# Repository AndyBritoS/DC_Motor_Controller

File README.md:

# DC_Motor_Controller
DC Motor Controller PCB Project files

This project was made following the PCB Design Mastery course from Fresu Electronics (https://www.fresuelectronics.com/) and it is for demonstration purpose only. The hardware was not built or tested. Some design aspects were ignored.

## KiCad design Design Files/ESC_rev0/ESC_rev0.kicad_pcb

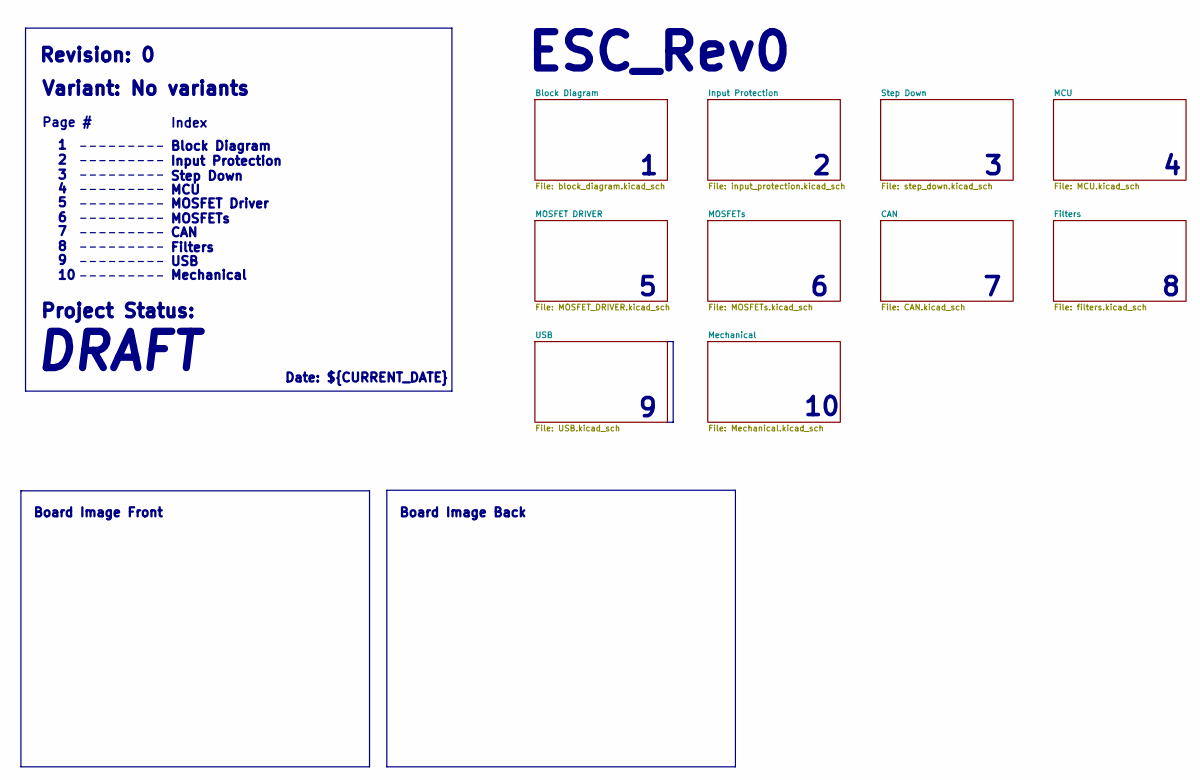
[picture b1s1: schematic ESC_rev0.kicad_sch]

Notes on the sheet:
MOSFET Driver
${TITLE}
Filters
Block Diagram
Revision: ${REVISION}
USB
Index
DRAFT
Mechanical
Page #
MOSFETs
Step Down
Variant: No variants
CAN
Input Protection
MCU
Board Image Front
Date: ${CURRENT_DATE}
Board Image Back
Project Status:

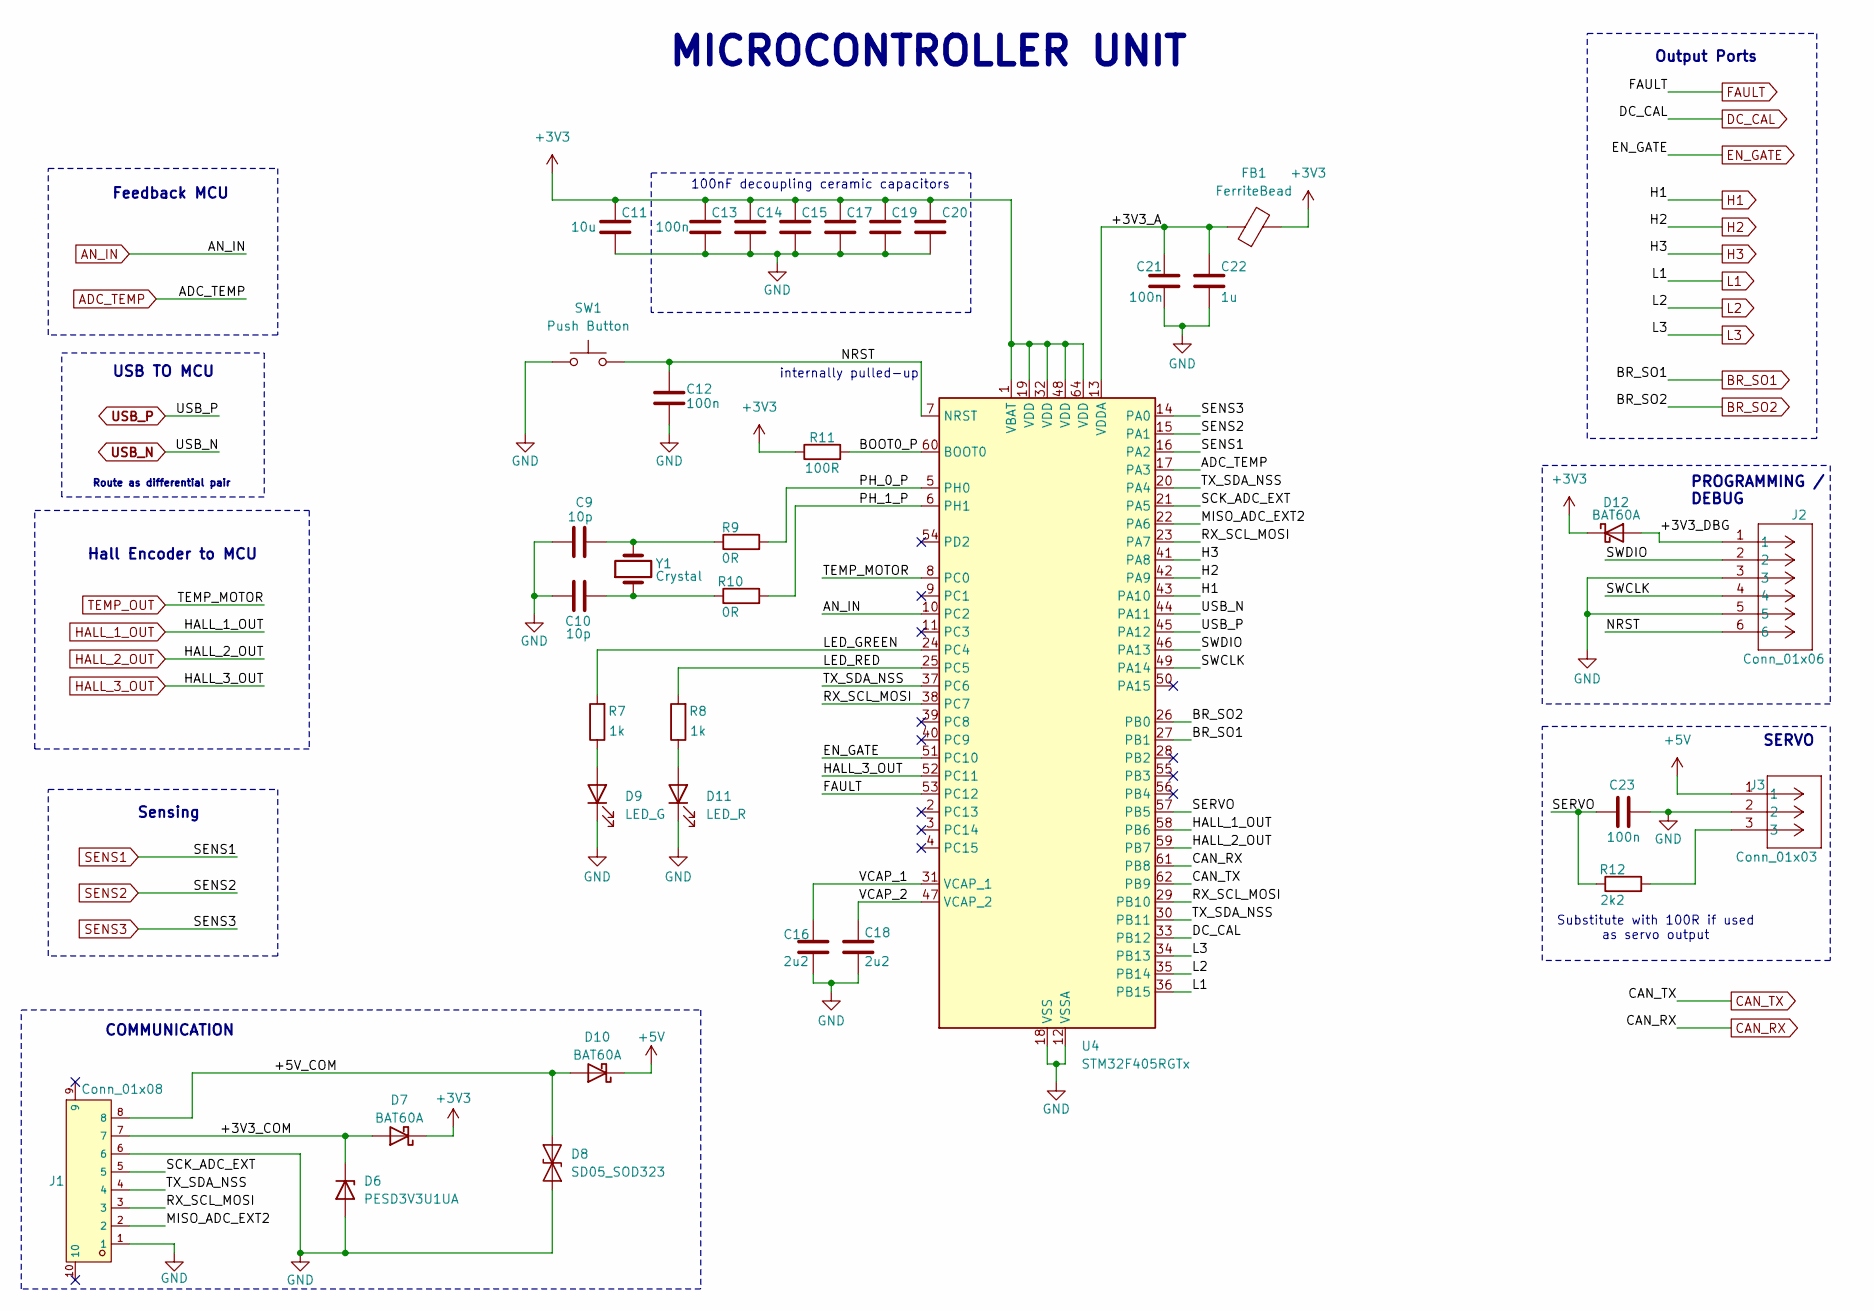
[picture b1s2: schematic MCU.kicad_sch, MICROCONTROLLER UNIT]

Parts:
C9, C10: 10p; C_0402_1005Metric
C11: 10u; C_0603_1608Metric
C12, C13, C14, C15, C17, C19, C20, C21, C23: 100n; C_0603_1608Metric
C16, C18: 2u2; C_0603_1608Metric
C22: 1u; C_0603_1608Metric
D6: PESD3V3U1UA; D_SOD-323F
D7, D10, D12: BAT60A; D_SOD-323
D8: SD05_SOD323; D_SOD-323
D9: LED_G; LED_0201_0603Metric
D11: LED_R; LED_0201_0603Metric
FB1: FerriteBead; L_0805_2012Metric
J1: Conn_01x08; CONN-SMD_8P-P2.50_HX25003-8AWB; LCSC C442367
J2: Conn_01x06; CONN_S6B-XH-SM4-TB_JST
J3: Conn_01x03; CONN3_S3B-XH_JST
R7, R8: 1k; R_0603_1608Metric
R9, R10: 0R; R_0603_1608Metric
R11: 100R; R_0603_1608Metric
R12: 2k2; R_0603_1608Metric
SW1: Push Button; SW_PTS636_SM43J_SMTR_LFS
U4: STM32F405RGTx; LQFP-64_10x10mm_P0.5mm
Y1: Crystal; Crystal_SMD_2520-4Pin_2.5x2.0mm

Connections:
+3V3: C11.1, C13.1, C14.1, C15.1, C17.1, C19.1, C20.1, D7.1 (K), D12.1 (K), FB1.2, R11.1, U4.1 (VBAT), U4.19 (VDD), U4.32 (VDD), U4.48 (VDD), U4.64 (VDD); also elsewhere on the board
+5V: D10.1 (K), J3.1; also elsewhere on the board
/MCU/+3V3_A: C21.1, C22.1, FB1.1, U4.13 (VDDA)
/MCU/+3V3_COM: D6.1 (K), D7.2 (A), J1.7
/MCU/+3V3_DBG: D12.2 (A), J2.1
/MCU/+5V_COM: D8.2 (A2), D10.2 (A), J1.8
/MCU/BOOT0_P: R11.2, U4.60 (BOOT0)
/MCU/LED_GREEN: R7.2, U4.24 (PC4)
/MCU/LED_RED: R8.2, U4.25 (PC5)
/MCU/MISO_ADC_EXT2: J1.2, U4.22 (PA6)
/MCU/NRST: C12.1, J2.6, SW1.2, U4.7 (NRST)
/MCU/PH_0_P: R9.2, U4.5 (PH0)
/MCU/PH_1_P: R10.2, U4.6 (PH1)
/MCU/RX_SCL_MOSI: J1.3, U4.23 (PA7), U4.29 (PB10), U4.38 (PC7)
/MCU/SCK_ADC_EXT: J1.5, U4.21 (PA5)
/MCU/SERVO: C23.1, R12.1, U4.57 (PB5)
/MCU/SWCLK: J2.4, U4.49 (PA14)
/MCU/SWDIO: J2.2, U4.46 (PA13)
/MCU/TX_SDA_NSS: J1.4, U4.20 (PA4), U4.30 (PB11), U4.37 (PC6)
/MCU/VCAP_1: C16.1, U4.31 (VCAP_1)
/MCU/VCAP_2: C18.1, U4.47 (VCAP_2)
ADC_TEMP: U4.17 (PA3); also elsewhere on the board
AN_IN: U4.10 (PC2); also elsewhere on the board
BR_SO1: U4.27 (PB1); also elsewhere on the board
BR_SO2: U4.26 (PB0); also elsewhere on the board
CAN_RX: U4.61 (PB8); also elsewhere on the board
CAN_TX: U4.62 (PB9); also elsewhere on the board
DC_CAL: U4.33 (PB12); also elsewhere on the board
EN_GATE: U4.51 (PC10); also elsewhere on the board
FAULT: U4.53 (PC12); also elsewhere on the board
GND: C9.1, C10.1, C11.2, C12.2, C13.2, C14.2, C15.2, C16.2, C17.2, C18.2, C19.2, C20.2, C21.2, C22.2, C23.2, D6.2 (A), D8.1 (A1), D9.1 (K), D11.1 (K), J1.1, J1.6, J2.3, J2.5, J3.2, SW1.1, U4.12 (VSSA), U4.18 (VSS), U4.63 (VSS); also elsewhere on the board
H1: U4.43 (PA10); also elsewhere on the board
H2: U4.42 (PA9); also elsewhere on the board
H3: U4.41 (PA8); also elsewhere on the board
HALL_1_OUT: U4.58 (PB6); also elsewhere on the board
HALL_2_OUT: U4.59 (PB7); also elsewhere on the board
HALL_3_OUT: U4.52 (PC11); also elsewhere on the board
L1: U4.36 (PB15); also elsewhere on the board
L2: U4.35 (PB14); also elsewhere on the board
L3: U4.34 (PB13); also elsewhere on the board
unnamed: C9.2, R9.1, Y1.2
unnamed: C10.2, R10.1, Y1.1
unnamed: D9.2 (A), R7.1
unnamed: D11.2 (A), R8.1
unnamed: J3.3, R12.2
SENS1: U4.16 (PA2); also elsewhere on the board
SENS2: U4.15 (PA1); also elsewhere on the board
SENS3: U4.14 (PA0); also elsewhere on the board
TEMP_OUT: U4.8 (PC0); also elsewhere on the board
USB_N: U4.44 (PA11); also elsewhere on the board
USB_P: U4.45 (PA12); also elsewhere on the board

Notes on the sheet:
Substitute with 100R if used as servo output
internally pulled-up
Hall Encoder to MCU
Output Ports
USB TO MCU
Feedback MCU
PROGRAMMING / DEBUG
SERVO
${TITLE}
COMMUNICATION
100nF decoupling ceramic capacitors
Route as differential pair
Sensing

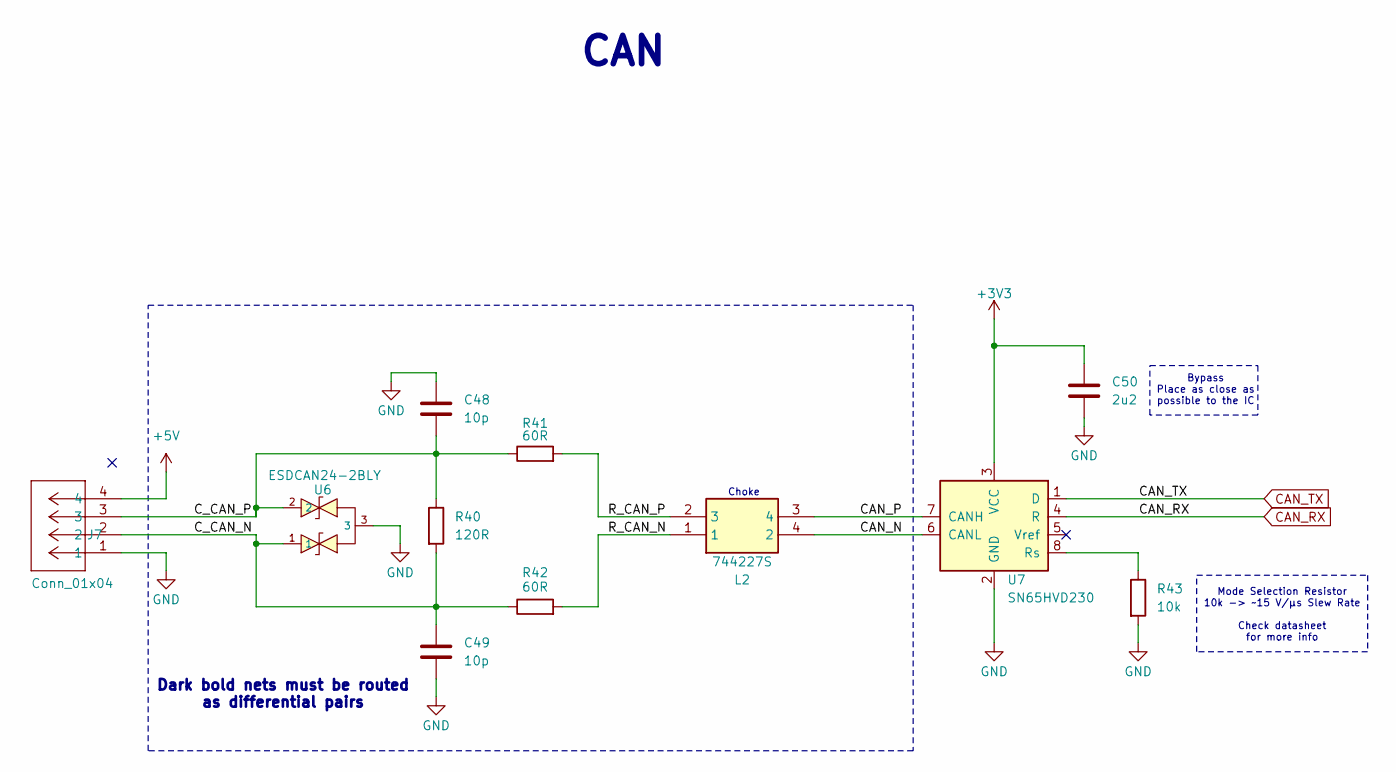
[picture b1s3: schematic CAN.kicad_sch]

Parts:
C48, C49: 10p; C_0603_1608Metric
C50: 2u2; C_0603_1608Metric
J7: Conn_01x04; CONN4_S4B-XH_JST
L2: 744227S; WE-SL274; Manufacturer_Part_Number 744227S; Mouser Part Number 710-744227S
R40: 120R; R_0603_1608Metric
R41, R42: 60R; R_0603_1608Metric
R43: 10k; R_0603_1608Metric
U6: ESDCAN24-2BLY; SOT-23-3_L3.0-W1.7-P0.95-LS2.9-BR; LCSC C246766
U7: SN65HVD230; SOIC-8_3.9x4.9mm_P1.27mm

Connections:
+3V3: C50.1, U7.3 (VCC); also elsewhere on the board
+5V: J7.4; also elsewhere on the board
/CAN/CAN_N: L2.4 (2), U7.6 (CANL)
/CAN/CAN_P: L2.3 (4), U7.7 (CANH)
/CAN/C_CAN_N: C49.1, J7.2, R40.2, R42.1, U6.1
/CAN/C_CAN_P: C48.2, J7.3, R40.1, R41.1, U6.2
/CAN/R_CAN_N: L2.1, R42.2
/CAN/R_CAN_P: L2.2 (3), R41.2
CAN_RX: U7.4 (R); also elsewhere on the board
CAN_TX: U7.1 (D); also elsewhere on the board
GND: C48.1, C49.2, C50.2, J7.1, R43.2, U6.3, U7.2 (GND); also elsewhere on the board
unnamed: R43.1, U7.8 (Rs)

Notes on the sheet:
Dark bold nets must be routed as differential pairs
Mode Selection Resistor 10k -> ~15 V/µs Slew Rate Check datasheet for more info
Bypass Place as close as possible to the IC
${TITLE}
Choke

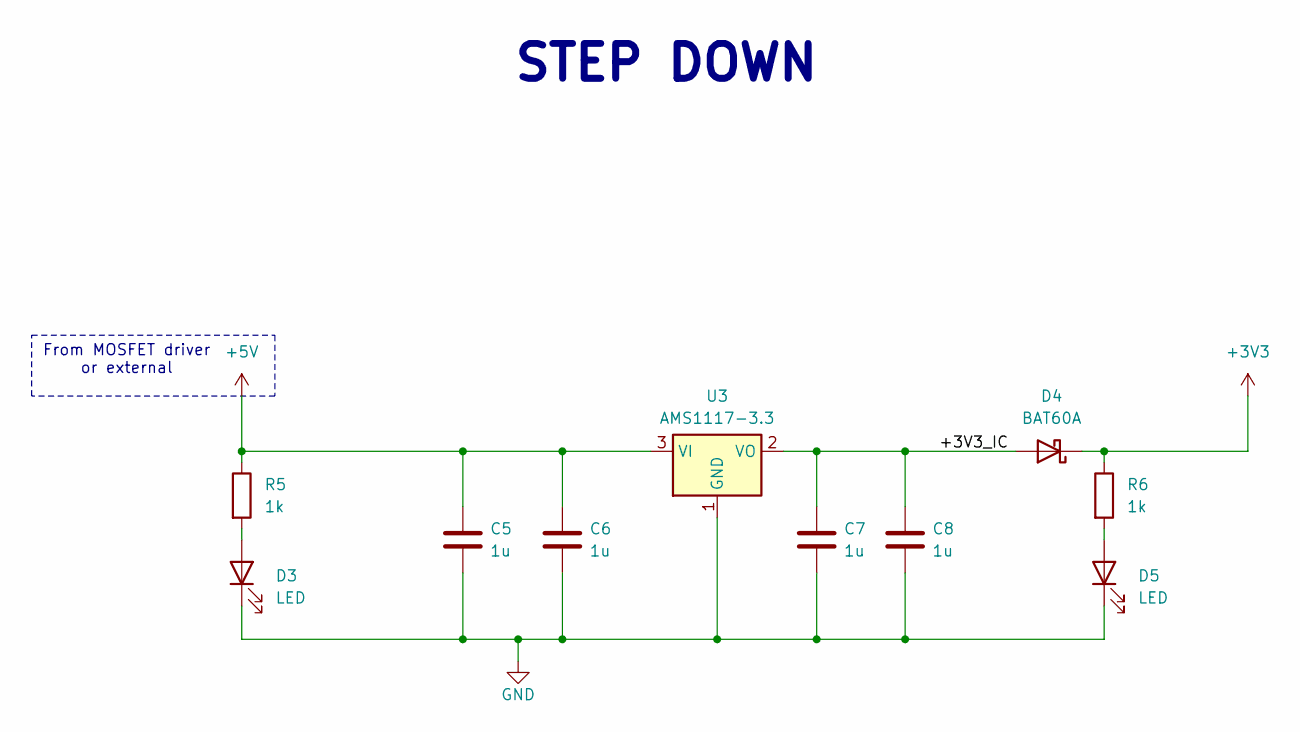
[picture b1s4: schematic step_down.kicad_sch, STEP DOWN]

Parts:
C5, C6, C7, C8: 1u; C_0603_1608Metric
D3, D5: LED; LED_0805_2012Metric
D4: BAT60A; D_SOD-323
R5, R6: 1k; R_0603_1608Metric
U3: AMS1117-3.3; SOT-223-3_TabPin2

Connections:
+3V3: D4.1 (K), R6.1; also elsewhere on the board
+5V: C5.1, C6.1, R5.1, U3.3 (VI); also elsewhere on the board
/Step Down/+3V3_IC: C7.1, C8.1, D4.2 (A), U3.2 (VO)
GND: C5.2, C6.2, C7.2, C8.2, D3.1 (K), D5.1 (K), U3.1 (GND); also elsewhere on the board
unnamed: D3.2 (A), R5.2
unnamed: D5.2 (A), R6.2

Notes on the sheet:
From MOSFET driver or external
${TITLE}

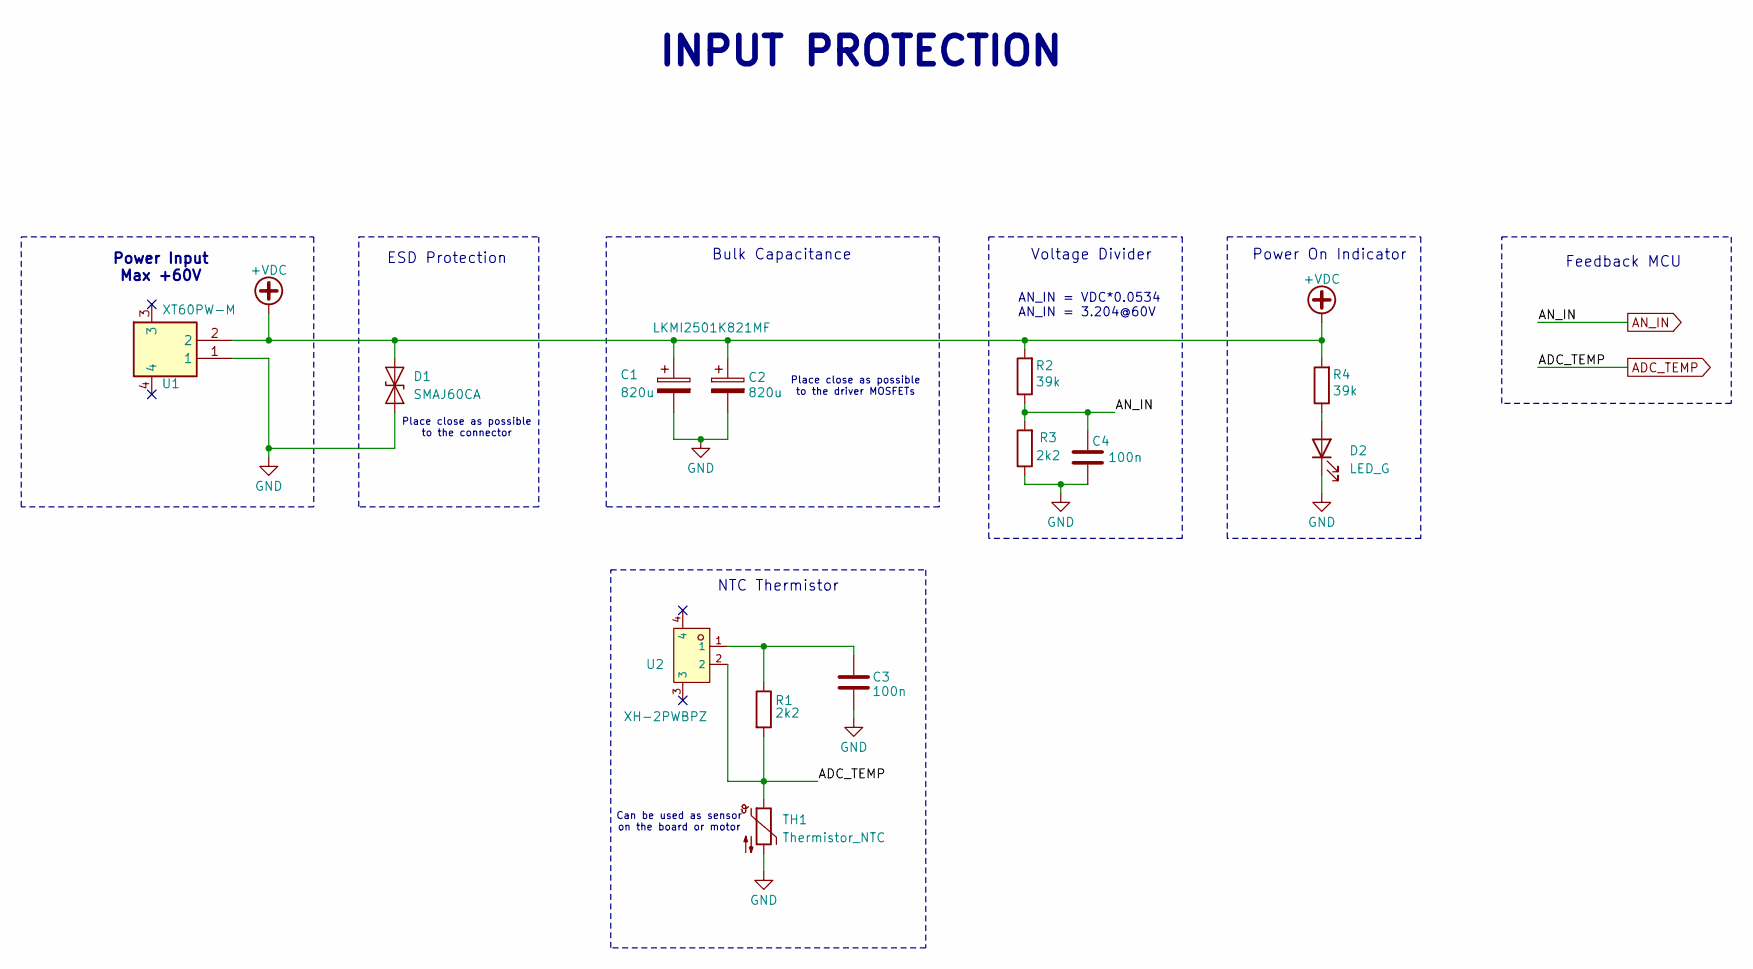
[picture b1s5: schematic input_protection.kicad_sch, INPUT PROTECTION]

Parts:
C1, C2: 820u; CP_Radial_D16.0mm_P7.50mm
C3, C4: 100n; C_0603_1608Metric
D1: SMAJ60CA; D_SMA
D2: LED_G; LED_0805_2012Metric
R1, R3: 2k2; R_0603_1608Metric
R2, R4: 39k; R_0603_1608Metric
TH1: Thermistor_NTC; C_0603_1608Metric_Pad1.08x0.95mm_HandSolder
U1: XT60PW-M; XT60PWM; Manufacturer_Part_Number XT60PW-M; LCSC C431092
U2: XH-2PWBPZ; CONN-SMD_XH-2PWBPZ; LCSC C2687444

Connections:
+VDC: C1.1, C2.1, D1.2 (A2), R2.2, R4.2, U1.2; also elsewhere on the board
ADC_TEMP: R1.2, TH1.1, U2.2; also elsewhere on the board
AN_IN: C4.1, R2.1, R3.2; also elsewhere on the board
GND: C1.2, C2.2, C3.2, C4.2, D1.1 (A1), D2.1 (K), R3.1, TH1.2, U1.1; also elsewhere on the board
unnamed: C3.1, R1.1, U2.1
unnamed: D2.2 (A), R4.1

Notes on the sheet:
Place close as possible to the driver MOSFETs
Place close as possible to the connector
Voltage Divider
AN_IN = VDC*0.0534 AN_IN = 3.204@60V
Can be used as sensor on the board or motor
Feedback MCU
Power Input Max +60V
${TITLE}
NTC Thermistor
Power On Indicator
ESD Protection
Bulk Capacitance

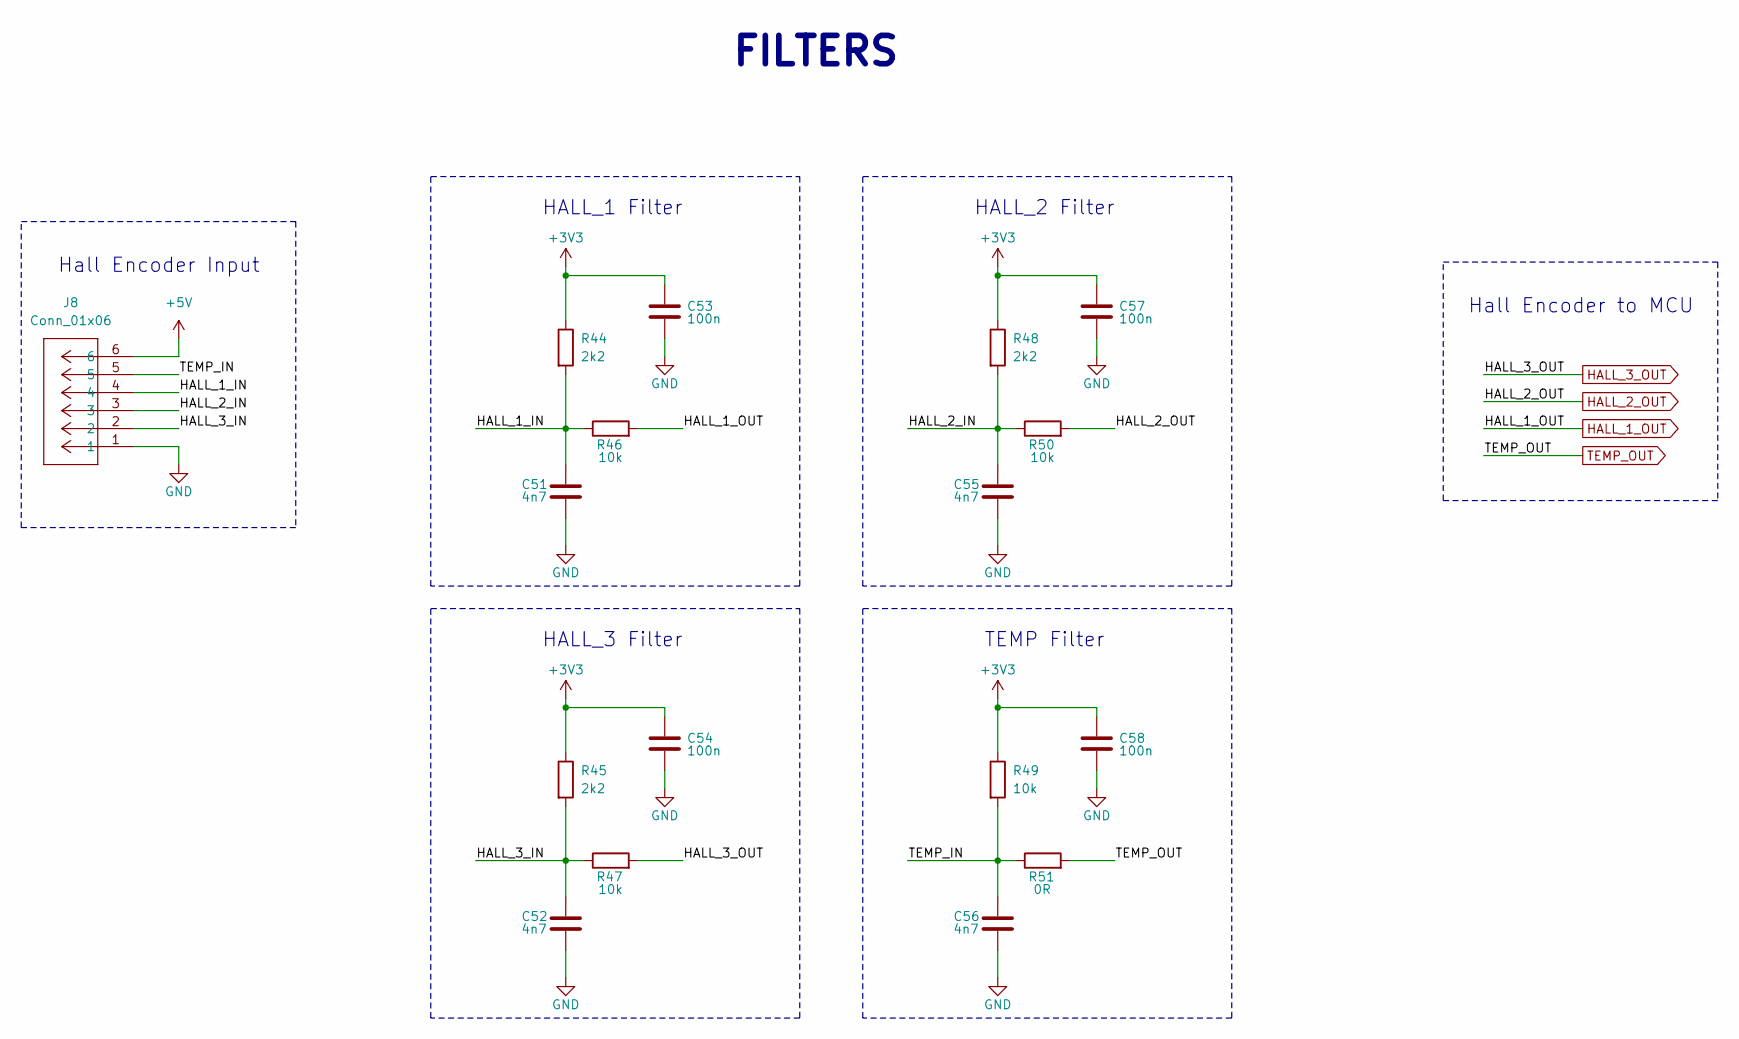
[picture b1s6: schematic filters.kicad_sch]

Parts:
C51, C52, C55, C56: 4n7; C_0603_1608Metric
C53, C54, C57, C58: 100n; C_0603_1608Metric
J8: Conn_01x06; CONN_S6B-XH-SM4-TB_JST
R44, R45, R48: 2k2; R_0603_1608Metric
R46, R47, R49, R50: 10k; R_0603_1608Metric
R51: 0R; R_0603_1608Metric

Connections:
+3V3: C53.1, C54.1, C57.1, C58.1, R44.1, R45.1, R48.1, R49.1; also elsewhere on the board
+5V: J8.6; also elsewhere on the board
/Filters/HALL_1_IN: C51.1, J8.4, R44.2, R46.1
/Filters/HALL_2_IN: C55.1, J8.3, R48.2, R50.1
/Filters/HALL_3_IN: C52.1, J8.2, R45.2, R47.1
/Filters/TEMP_IN: C56.1, J8.5, R49.2, R51.1
GND: C51.2, C52.2, C53.2, C54.2, C55.2, C56.2, C57.2, C58.2, J8.1; also elsewhere on the board
HALL_1_OUT: R46.2; also elsewhere on the board
HALL_2_OUT: R50.2; also elsewhere on the board
HALL_3_OUT: R47.2; also elsewhere on the board
TEMP_OUT: R51.2; also elsewhere on the board

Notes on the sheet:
HALL_1 Filter
Hall Encoder Input
HALL_3 Filter
HALL_2 Filter
${TITLE}
TEMP Filter
Hall Encoder to MCU

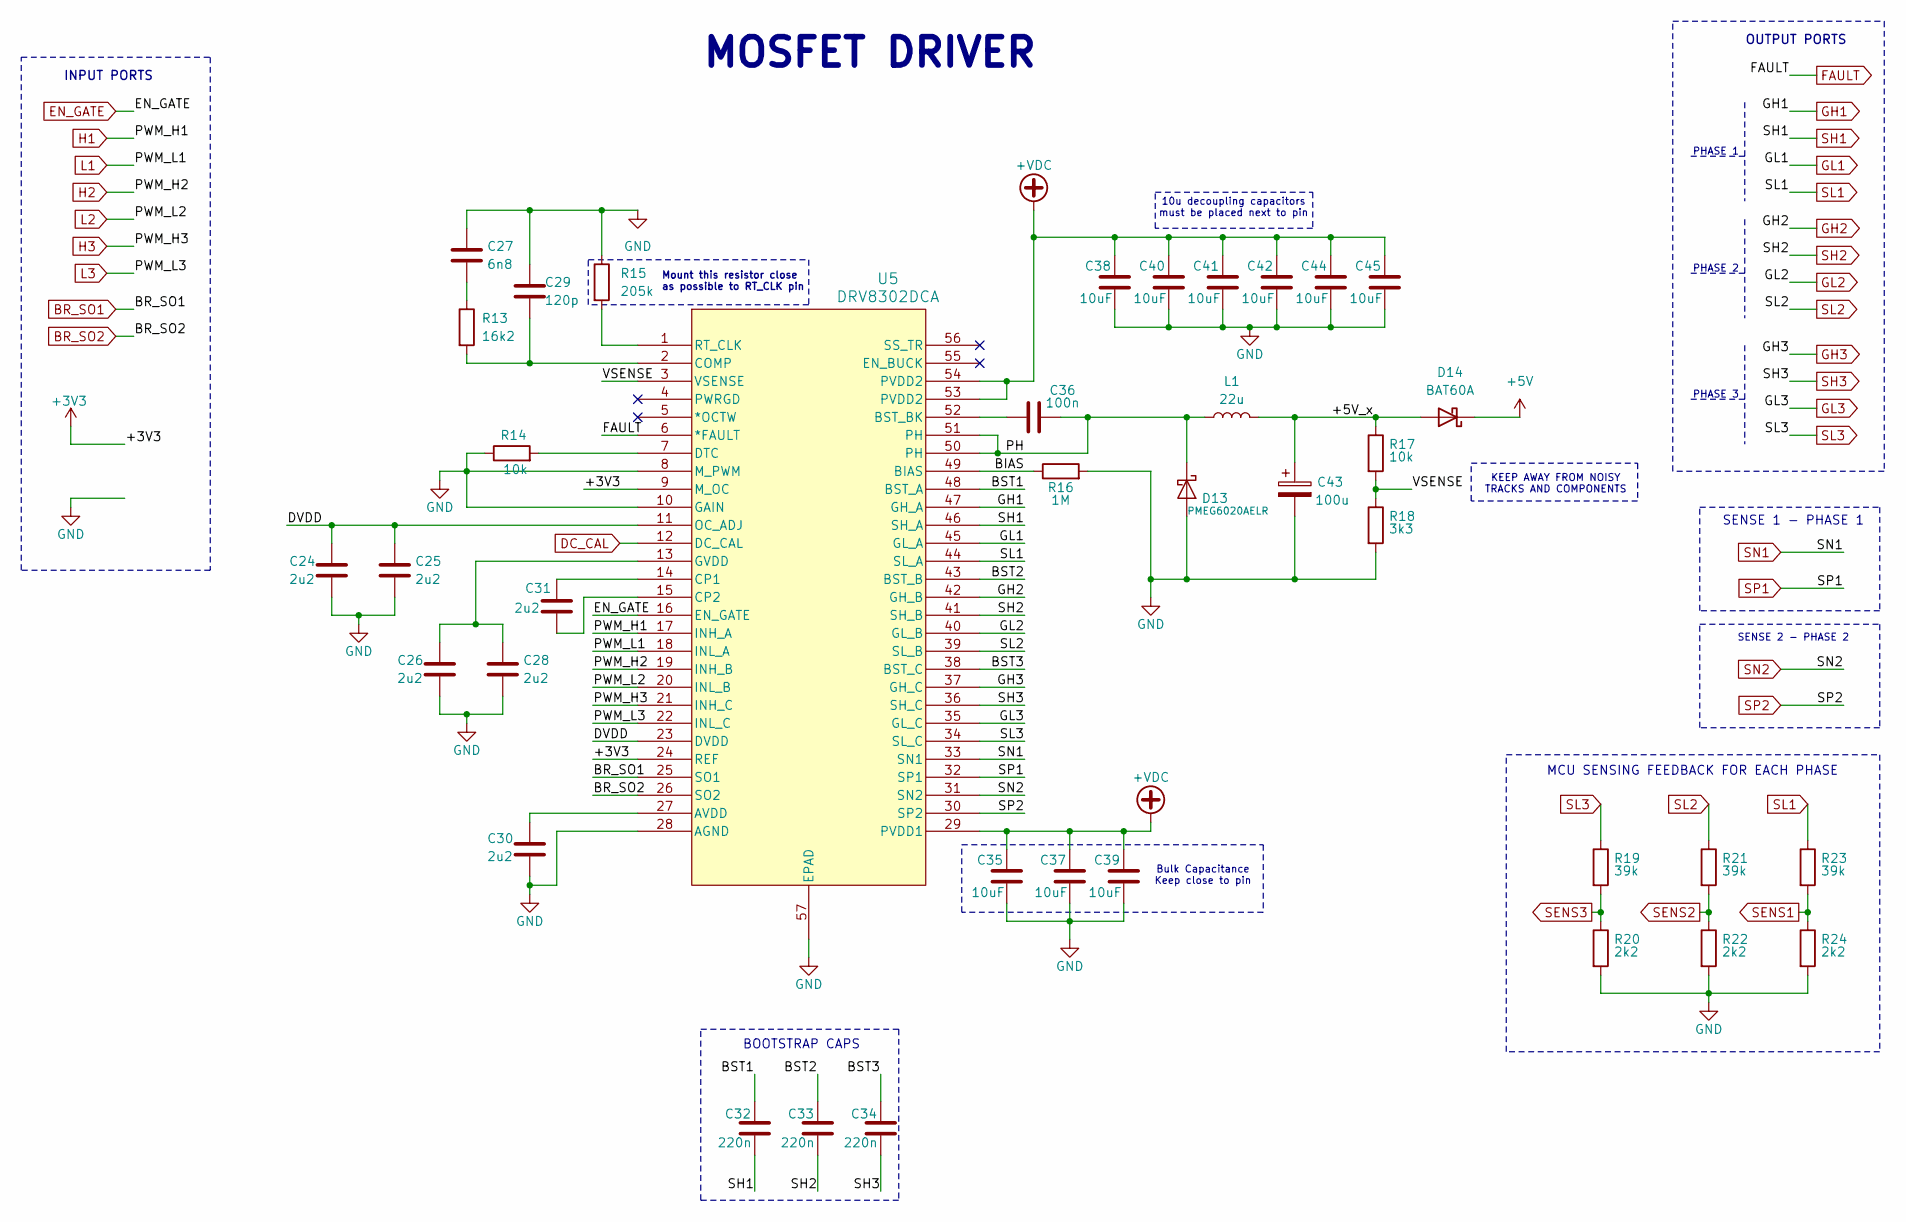
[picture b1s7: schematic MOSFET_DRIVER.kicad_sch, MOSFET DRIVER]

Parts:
C24, C25, C26, C28, C30, C31: 2u2; C_0603_1608Metric
C27: 6n8; C_0603_1608Metric
C29: 120p; C_0603_1608Metric
C32, C33, C34: 220n; C_0603_1608Metric
C35, C37, C38, C39, C40, C41, C42, C44, C45: 10uF; C_0603_1608Metric
C36: 100n; C_0603_1608Metric
C43: 100u; C_1210_3225Metric
D13: PMEG6020AELR; Nexperia_CFP3_SOD-123W
D14: BAT60A; D_SOD-323
L1: 22u; IND-SMD_L7.8-W7.8_SDR0805
R13: 16k2; R_0603_1608Metric
R14, R17: 10k; R_0603_1608Metric
R15: 205k; R_0603_1608Metric
R16: 1M; R_0603_1608Metric
R18: 3k3; R_0603_1608Metric
R19, R21, R23: 39k; R_0603_1608Metric
R20, R22, R24: 2k2; R_0603_1608Metric
U5: DRV8302DCA; DCA56_6P35X3P61

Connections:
+3V3: U5.9 (M_OC), U5.24 (REF); also elsewhere on the board
+5V: D14.1 (K); also elsewhere on the board
+VDC: C35.1, C37.1, C38.1, C39.1, C40.1, C41.1, C42.1, C44.1, C45.1, U5.29 (PVDD1), U5.53 (PVDD2), U5.54 (PVDD2); also elsewhere on the board
/MOSFET DRIVER/+5V_x: C43.1, D14.2 (A), L1.2, R17.1
/MOSFET DRIVER/BIAS: R16.1, U5.49 (BIAS)
/MOSFET DRIVER/BST1: C32.1, U5.48 (BST_A)
/MOSFET DRIVER/BST2: C33.1, U5.43 (BST_B)
/MOSFET DRIVER/BST3: C34.1, U5.38 (BST_C)
/MOSFET DRIVER/DVDD: C24.1, C25.1, U5.11 (OC_ADJ), U5.23 (DVDD)
/MOSFET DRIVER/PH: C36.2, D13.1 (K), L1.1, U5.50 (PH), U5.51 (PH)
/MOSFET DRIVER/VSENSE: R17.2, R18.1, U5.3 (VSENSE)
BR_SO1: U5.25 (SO1); also elsewhere on the board
BR_SO2: U5.26 (SO2); also elsewhere on the board
DC_CAL: U5.12 (DC_CAL); also elsewhere on the board
EN_GATE: U5.16 (EN_GATE); also elsewhere on the board
FAULT: U5.6 (*FAULT); also elsewhere on the board
GH1: U5.47 (GH_A); also elsewhere on the board
GH2: U5.42 (GH_B); also elsewhere on the board
GH3: U5.37 (GH_C); also elsewhere on the board
GL1: U5.45 (GL_A); also elsewhere on the board
GL2: U5.40 (GL_B); also elsewhere on the board
GL3: U5.35 (GL_C); also elsewhere on the board
GND: C24.2, C25.2, C26.2, C27.1, C28.2, C29.1, C30.2, C35.2, C37.2, C38.2, C39.2, C40.2, C41.2, C42.2, C43.2, C44.2, C45.2, D13.2 (A), R14.1, R15.1, R16.2, R18.2, R20.2, R22.2, R24.2, U5.8 (M_PWM), U5.10 (GAIN), U5.28 (AGND), U5.57 (EPAD), U5.V; also elsewhere on the board
H1: U5.17 (INH_A); also elsewhere on the board
H2: U5.19 (INH_B); also elsewhere on the board
H3: U5.21 (INH_C); also elsewhere on the board
L1: U5.18 (INL_A); also elsewhere on the board
L2: U5.20 (INL_B); also elsewhere on the board
L3: U5.22 (INL_C); also elsewhere on the board
unnamed: C27.2, R13.1
unnamed: C30.1, U5.27 (AVDD)
unnamed: C36.1, U5.52 (BST_BK)
unnamed: C29.2, R13.2, U5.2 (COMP)
unnamed: C31.1, U5.14 (CP1)
unnamed: C31.2, U5.15 (CP2)
unnamed: R14.2, U5.7 (DTC)
unnamed: C26.1, C28.1, U5.13 (GVDD)
unnamed: R15.2, U5.1 (RT_CLK)
SENS1: R23.2, R24.1; also elsewhere on the board
SENS2: R21.2, R22.1; also elsewhere on the board
SENS3: R19.2, R20.1; also elsewhere on the board
SH1: C32.2, U5.46 (SH_A); also elsewhere on the board
SH2: C33.2, U5.41 (SH_B); also elsewhere on the board
SH3: C34.2, U5.36 (SH_C); also elsewhere on the board
SL1: R23.1, U5.44 (SL_A); also elsewhere on the board
SL2: R21.1, U5.39 (SL_B); also elsewhere on the board
SL3: R19.1, U5.34 (SL_C); also elsewhere on the board
SN1: U5.33 (SN1); also elsewhere on the board
SN2: U5.31 (SN2); also elsewhere on the board
SP1: U5.32 (SP1); also elsewhere on the board
SP2: U5.30 (SP2); also elsewhere on the board

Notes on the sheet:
Mount this resistor close as possible to RT_CLK pin
PHASE 2
SENSE 1 - PHASE 1
SENSE 2 - PHASE 2
10u decoupling capacitors must be placed next to pin
OUTPUT PORTS
MCU SENSING FEEDBACK FOR EACH PHASE
INPUT PORTS
${TITLE}
PHASE 1
Bulk Capacitance Keep close to pin
BOOTSTRAP CAPS
PHASE 3
KEEP AWAY FROM NOISY TRACKS AND COMPONENTS

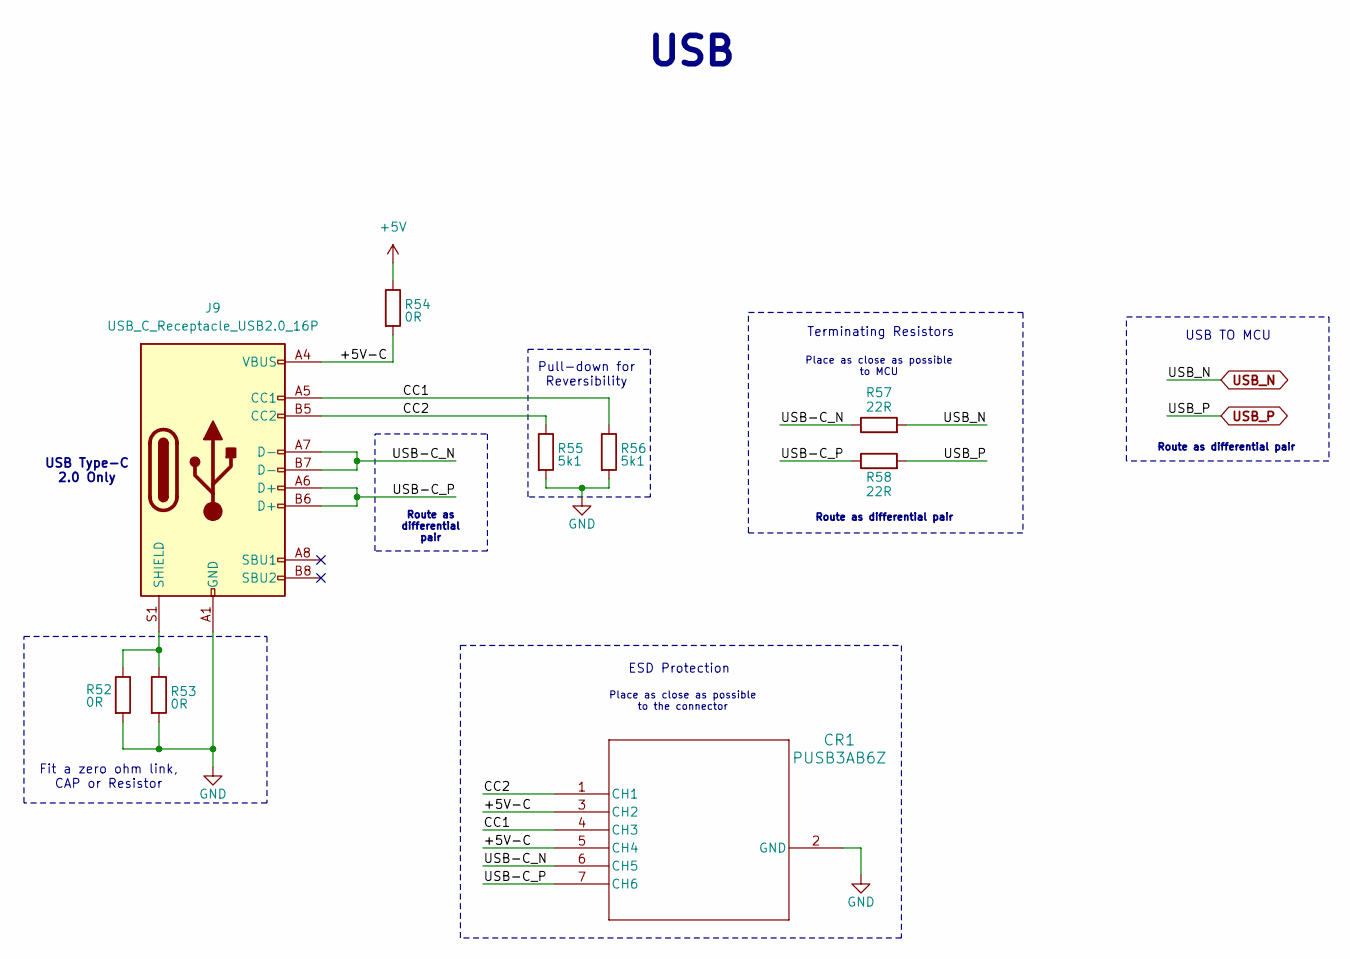
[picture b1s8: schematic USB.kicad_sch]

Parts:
CR1: PUSB3AB6Z; PUSB3AB6Z_NEX
J9: USB_C_Receptacle_USB2.0_16P; USB_C_Receptacle_GCT_USB4105-xx-A_16P_TopMnt_Horizontal_mod
R52, R53, R54: 0R; R_0603_1608Metric
R55, R56: 5k1; R_0603_1608Metric
R57, R58: 22R; R_0603_1608Metric

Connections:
+5V: R54.1; also elsewhere on the board
/USB/+5V-C: CR1.3 (CH2), CR1.5 (CH4), J9.A4 (VBUS), J9.A9 (VBUS), J9.B4 (VBUS), J9.B9 (VBUS), R54.2
/USB/CC1: CR1.4 (CH3), J9.A5 (CC1), R56.1
/USB/CC2: CR1.1 (CH1), J9.B5 (CC2), R55.1
/USB/USB-C_N: CR1.6 (CH5), J9.A7 (D-), J9.B7 (D-), R57.1
/USB/USB-C_P: CR1.7 (CH6), J9.A6 (D+), J9.B6 (D+), R58.1
GND: CR1.2 (GND), J9.A1 (GND), J9.A12 (GND), J9.B1 (GND), J9.B12 (GND), R52.2, R53.2, R55.2, R56.2; also elsewhere on the board
unnamed: J9.S1 (SHIELD), R52.1, R53.1
USB_N: R57.2; also elsewhere on the board
USB_P: R58.2; also elsewhere on the board

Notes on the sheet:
ESD Protection
USB TO MCU
Pull-down for Reversibility
Terminating Resistors
Route as differential pair
Place as close as possible to MCU
USB Type-C 2.0 Only
Fit a zero ohm link, CAP or Resistor
Route as differential pair
Place as close as possible to the connector
${TITLE}

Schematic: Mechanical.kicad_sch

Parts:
H1, H2, H3, H4: MountingHole_Pad; MountingHole_3.2mm_M3_Pad_Via
R59, R60, R61, R62: 0R; R_0603_1608Metric

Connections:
GND: R59.2, R60.2, R61.2, R62.2; also elsewhere on the board
unnamed: H1.1, R59.1
unnamed: H2.1, R60.1
unnamed: H3.1, R61.1
unnamed: H4.1, R62.1

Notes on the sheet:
Date
Logo_no_slk
Logos
- Thermistor moved to lower terminal of the ADC pin - Boot pin pulled-down - Changed bulk capacitance - Changed phase sense resistors - Changed net sense phases to differential pairs - Inverted Tx and Rx connector pins
Modifications from VESC 4.11
Labels
QR Code
Mounting Holes
Layer 2 - Inner GND
Notes
Logo
Fit a zero ohm link, Cap or Resistor
Layer 3 - Inner GND
${TITLE}
Layer 4 - Back
Layer 1 - Front
Board Name

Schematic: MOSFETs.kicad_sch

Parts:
C46, C47: 2n2; C_0603_1608Metric
J4, J5, J6: WP-BUTR; 7461084
NT1, NT2, NT5: NetTie_2; NetTie-2_SMD_Pad2.00mm_Small
NT3, NT4, NT6, NT7, NT8: NetTie_2; NetTie-2_SMD_Pad2.0mm
Q1, Q2, Q3, Q4, Q5, Q6: HSBA15810C; PQFN-8_L6.0-W5.0-P1.27-LS6.0-BL; LCSC C845605
R25, R26, R31, R32, R37, R38: 4R7; R_0603_1608Metric
R27, R28, R33, R34: 100R; R_0603_1608Metric
R29, R35, R39: 39k; R_0603_1608Metric
R30, R36: FKM5R0005FE-TR; RES-SMD_4P-L6.9-W6.6_OHMITE_FKM5RXXXXFE-TR; LCSC C2482696

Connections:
+VDC: Q1.5 (D), Q1.6 (D), Q1.7 (D), Q1.8 (D), Q1.9 (D), Q3.5 (D), Q3.6 (D), Q3.7 (D), Q3.8 (D), Q3.9 (D), Q5.5 (D), Q5.6 (D), Q5.7 (D), Q5.8 (D), Q5.9 (D); also elsewhere on the board
/MOSFETs/GH1_RG: Q1.4 (G), R25.2
/MOSFETs/GH2_RG: Q3.4 (G), R31.2
/MOSFETs/GH3_RG: Q5.4 (G), R37.2
/MOSFETs/GL1_RG: Q2.4 (G), R26.2, R29.1
/MOSFETs/GL2_RG: Q4.4 (G), R32.2, R35.1
/MOSFETs/GL3_RG: Q6.4 (G), R38.2, R39.1
/MOSFETs/PHASE_1: J4.1, NT1.2, Q1.1 (S), Q1.2 (S), Q1.3 (S), Q2.5 (D), Q2.6 (D), Q2.7 (D), Q2.8 (D), Q2.9 (D)
/MOSFETs/PHASE_2: J5.1, NT4.2, Q3.1 (S), Q3.2 (S), Q3.3 (S), Q4.5 (D), Q4.6 (D), Q4.7 (D), Q4.8 (D), Q4.9 (D)
/MOSFETs/PHASE_3: J6.1, NT7.2, Q5.1 (S), Q5.2 (S), Q5.3 (S), Q6.5 (D), Q6.6 (D), Q6.7 (D), Q6.8 (D), Q6.9 (D)
/MOSFETs/S1_N: R28.2, R30.4
/MOSFETs/S1_P: R27.2, R30.3
/MOSFETs/S2_N: R34.2, R36.4
/MOSFETs/S2_P: R33.2, R36.3
GH1: R25.1; also elsewhere on the board
GH2: R31.1; also elsewhere on the board
GH3: R37.1; also elsewhere on the board
GL1: R26.1; also elsewhere on the board
GL2: R32.1; also elsewhere on the board
GL3: R38.1; also elsewhere on the board
GND: NT3.1, NT6.1, NT8.1, R29.2, R35.2, R39.2; also elsewhere on the board
unnamed: NT2.1, R30.2
unnamed: NT3.2, R30.1
unnamed: NT5.1, R36.2
unnamed: NT6.2, R36.1
SH1: NT1.1; also elsewhere on the board
SH2: NT4.1; also elsewhere on the board
SH3: NT7.1; also elsewhere on the board
SL1: NT2.2, Q2.1 (S), Q2.2 (S), Q2.3 (S); also elsewhere on the board
SL2: NT5.2, Q4.1 (S), Q4.2 (S), Q4.3 (S); also elsewhere on the board
SL3: NT8.2, Q6.1 (S), Q6.2 (S), Q6.3 (S); also elsewhere on the board
SN1: C46.1, R27.1; also elsewhere on the board
SN2: C47.1, R33.1; also elsewhere on the board
SP1: C46.2, R28.1; also elsewhere on the board
SP2: C47.2, R34.1; also elsewhere on the board

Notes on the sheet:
ROUTE AS KEVIN CONNECTIONS
SENSE 1
Q_SOURCES
Place as close as possible to the bulk capacitance
SHx
PHASE 1
Q_CONTROL
${TITLE}
OUTPUT PHASE 1
OUTPUT PHASE 3
ROUTE AS KELVIN CONNECTIONS
OUTPUT PHASE 2
SENSE 2
PHASE 2

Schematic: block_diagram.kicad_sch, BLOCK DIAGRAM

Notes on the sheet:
Page 5
Page 8
Page 6
Page 3
8 - 60 V
+3V3
Page 7
COM
MOTOR
USB
STEP-DOWN 3V3
Page 4
CAN
Page 2
${TITLE}
+VDC
MCU
+5V
MOSFET DRIVER
MOSFETs
SERVO
Page 9
HALL/ENCODER
TEMP_SENSOR
